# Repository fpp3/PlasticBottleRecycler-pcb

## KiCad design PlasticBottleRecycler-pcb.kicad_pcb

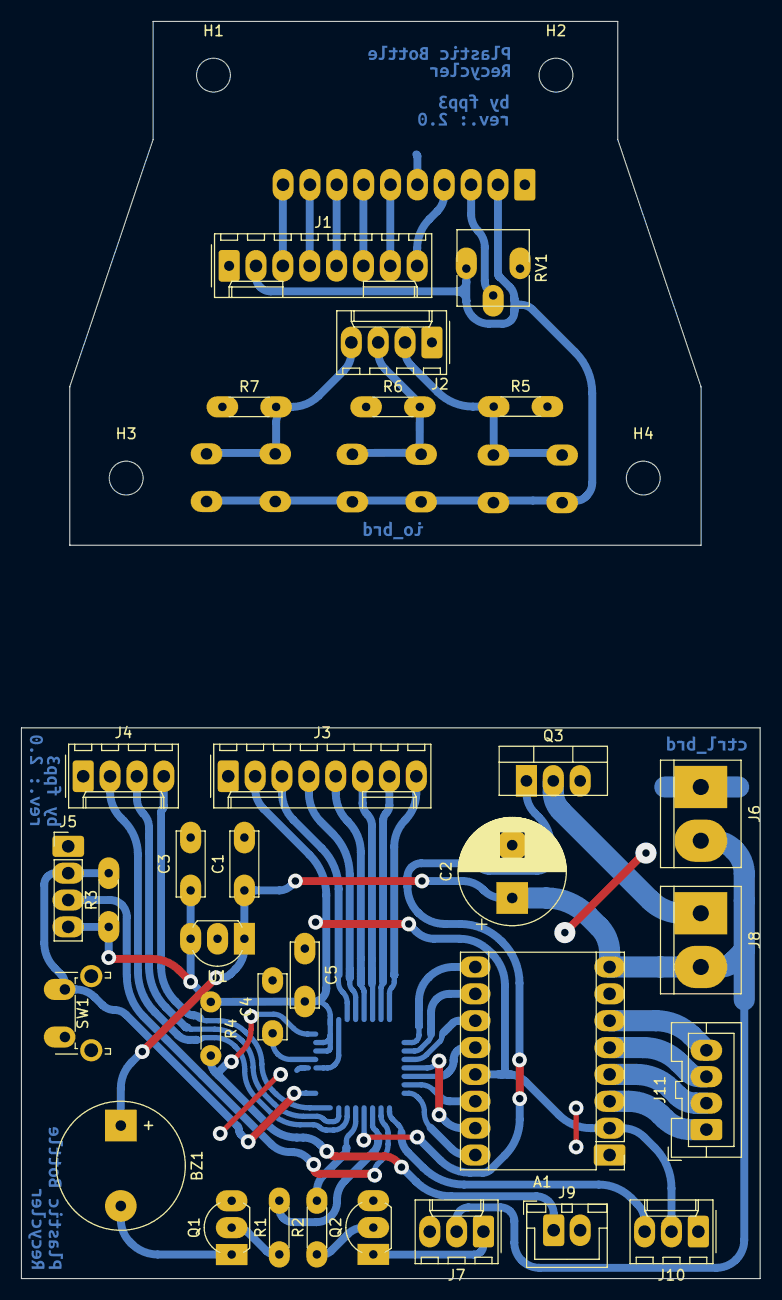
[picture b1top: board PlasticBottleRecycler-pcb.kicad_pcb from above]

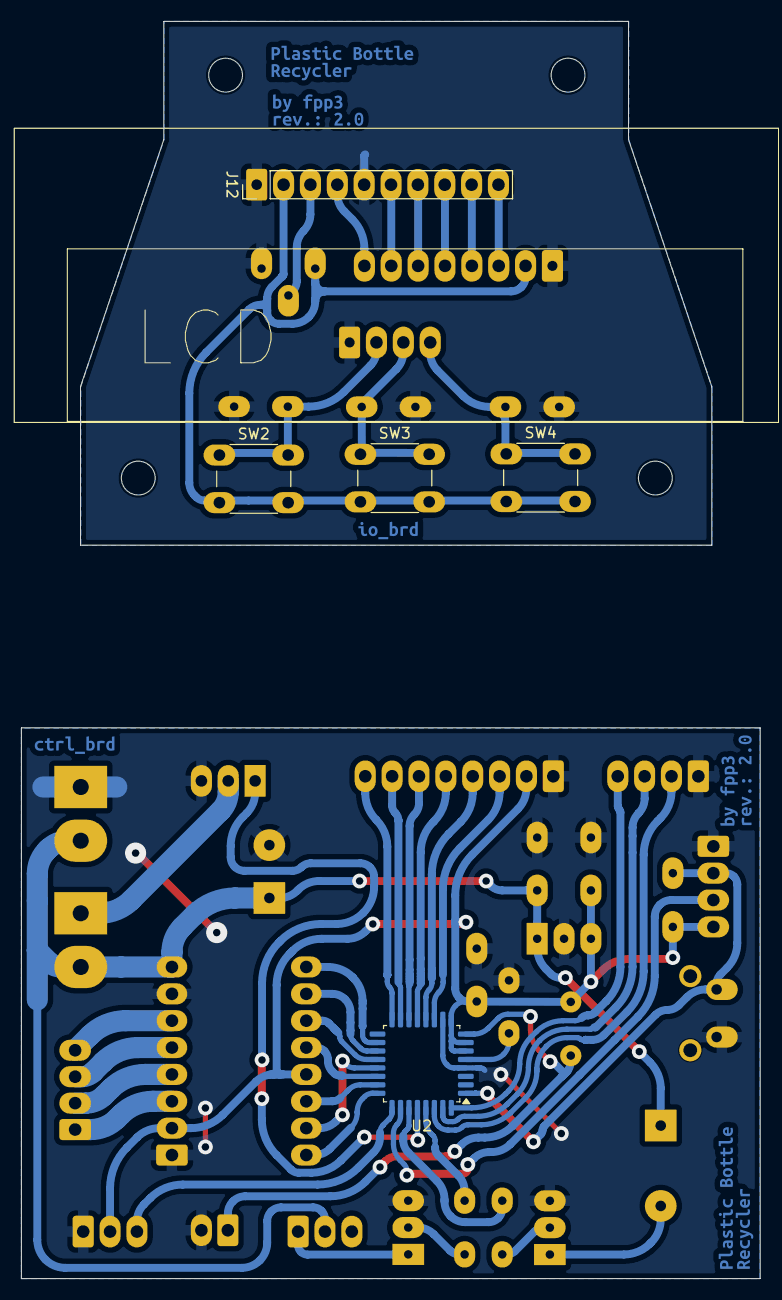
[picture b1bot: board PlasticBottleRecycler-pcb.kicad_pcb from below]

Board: 2 copper layers, 69.8 x 118.9 mm, 46 parts (11 on the bottom side), 48 nets.

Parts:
A1: Pololu_Breakout_A4988; Pololu_Breakout-16_15.2x20.3mm
BZ1: Buzzer; Buzzer_12x9.5RM7.6
C1: 330nF; C_Disc_D6.0mm_W2.5mm_P5.00mm
C2: 1000u; CP_Radial_D10.0mm_P5.00mm
C3: 100nF; C_Disc_D6.0mm_W2.5mm_P5.00mm
C4, C5: 100n; C_Disc_D6.0mm_W2.5mm_P5.00mm
H1, H2, H3, H4: MountingHole; MountingHole_3.2mm_M3
J1, J3: Conn_01x08; Molex_KK-254_AE-6410-08A_1x08_P2.54mm_Vertical
J2, J4: Conn_01x04; Molex_KK-254_AE-6410-04A_1x04_P2.54mm_Vertical
J5: SWIM; PinHeader_1x04_P2.54mm_Vertical
J6: +12V; TerminalBlock_bornier-2_P5.08mm
J7: FAN1; Molex_KK-254_AE-6410-03A_1x03_P2.54mm_Vertical
J8: HEATER; TerminalBlock_bornier-2_P5.08mm
J9: NTC; JST_XH_B2B-XH-A_1x02_P2.50mm_Vertical
J10: RUNOUT; Molex_KK-254_AE-6410-03A_1x03_P2.54mm_Vertical
J11: STEPPER; JST_XA_B04B-XASK-1_1x04_P2.50mm_Vertical
J12: LCD; PinHeader_1x10_P2.54mm_Vertical
Q1, Q2: BC337; TO-92L_Inline_Wide
Q3: IRF3205; TO-220-3_Vertical
R1, R2: 680; R_Axial_DIN0204_L3.6mm_D1.6mm_P5.08mm_Horizontal
R3, R5, R6, R7: 10K; R_Axial_DIN0204_L3.6mm_D1.6mm_P5.08mm_Horizontal
R4: 4K7; R_Axial_DIN0204_L3.6mm_D1.6mm_P5.08mm_Horizontal
RV1: 100K; Potentiometer_Vishay_T73YP_Vertical
SW1: RESET; SW_Tactile_SPST_Angled_PTS645Vx39-2LFS
SW2: BTN_PLUS; SW_PUSH_6mm_H7.3mm
SW3: BTN_OK; SW_PUSH_6mm_H7.3mm
SW4: BTN_MINUS; SW_PUSH_6mm_H7.3mm
U1: LM7805_TO220; TO-92L_Inline_Wide
U2: STM8S005K6T6C; LQFP-32_7x7mm_P0.8mm
kibuzzard-67C3B0C4: G***; kibuzzard-67C3B0C4
kibuzzard-67C3947F: G***; kibuzzard-67C3947F
kibuzzard-67C39444, kibuzzard-67C39444#2: G***; kibuzzard-67C39444
kibuzzard-67C39452, kibuzzard-67C39452#2: G***; kibuzzard-67C39452

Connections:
/Controller Board/+5V: A1.2 (VDD), A1.13 (~RESET), C3.1, C5.2, J3.2, J5.4, J10.2, R3.1, R4.1, U1.3 (VO), U2.6 (VDD), U2.7 (VDDIO), U2.9 (VDDA)
/Controller Board/+12V: A1.8 (VMOT), BZ1.1 (+), C1.1, C2.1, J6.2, J7.2, J8.2, U1.1 (VI)
/Controller Board/A4988_DIR: A1.16 (DIR), U2.24 (SPI_MISO/PC7)
/Controller Board/A4988_ENA: A1.9 (~ENABLE), U2.18 (PC1/TIM1_CH1/UART2_CLK)
/Controller Board/A4988_MS1: A1.10 (MS1), U2.19 (PC2/TIM1_CH2)
/Controller Board/A4988_MS2: A1.11 (MS2), U2.20 (PC3/TIM1_CH3)
/Controller Board/A4988_MS3: A1.12 (MS3), U2.22 (SPI_SCK/PC5)
/Controller Board/A4988_SLP: A1.14 (~SLEEP), U2.23 (SPI_MOSI/PC6)
/Controller Board/A4988_STP: A1.15 (STEP), U2.21 (PC4/TIM1_CH4)
/Controller Board/BTN_MINUS: J4.4, U2.32 (TLI/TIM1_CH4/PD7)
/Controller Board/BTN_OK: J4.3, U2.31 (UART2_RX/PD6)
/Controller Board/BTN_PLUS: J4.2, U2.30 (UART2_TX/PD5)
/Controller Board/BUZZER: R1.1, U2.27 (TIM3_CH1/TIM2_CH3/PD2)
/Controller Board/FAN1: R2.1, U2.29 (TIM2_CH1/BEEP/PD4)
/Controller Board/GND: A1.1 (GND), A1.7 (GND), C1.2, C2.2, C3.2, C4.2, C5.1, J3.1, J4.1, J5.1, J6.1, J9.2, J10.1, Q1.3 (E), Q2.3 (E), Q3.3 (S), SW1.1, U1.2 (GND), U2.4 (VSS), U2.10 (VSSA)
/Controller Board/HEATER: Q3.1 (G), U2.28 (TIM2_CH2/ADC_ETR/PD3)
/Controller Board/LCD_D4: J3.6, U2.14 (PB2/TIM1_CH3N/AIN2)
/Controller Board/LCD_D5: J3.5, U2.13 (PB3/TIM1_ETR/AIN3)
/Controller Board/LCD_D6: J3.4, U2.12 (PB4/I2C_SCL/AIN4)
/Controller Board/LCD_D7: J3.3, U2.11 (PB5/I2C_SDA/AIN5)
/Controller Board/LCD_EN: J3.7, U2.15 (PB1/TIM1_CH2N/AIN1)
/Controller Board/LCD_RS: J3.8, U2.16 (PB0/TIM1_CH1N/AIN0)
/Controller Board/RESET: J5.2, R3.2, SW1.2, U2.1 (~RST)
/Controller Board/RUNOUT: J10.3, U2.25 (TIM3_CH2/TIM1_BKIN/CLK_CCO/PD0)
/Controller Board/SWIM: J5.3, U2.26 (SWIM/PD1)
/IO Board/+5V: J1.2, J12.2, RV1.1, SW2.2, SW3.2, SW4.2
/IO Board/BTN_MINUS: J2.4, R7.2, SW4.1
/IO Board/BTN_OK: J2.3, R6.2, SW3.1
/IO Board/BTN_PLUS: J2.2, R5.1, SW2.1
/IO Board/GND: J1.1, J2.1, J12.1, J12.5, R5.2, R6.1, R7.1, RV1.3
/IO Board/LCD_D4: J1.6, J12.7
/IO Board/LCD_D5: J1.5, J12.8
/IO Board/LCD_D6: J1.4, J12.9
/IO Board/LCD_D7: J1.3, J12.10
/IO Board/LCD_EN: J1.7, J12.6
/IO Board/LCD_RS: J1.8, J12.4
unnamed: A1.4 (1A), J11.2
unnamed: A1.3 (1B), J11.1
unnamed: A1.5 (2A), J11.3
unnamed: A1.6 (2B), J11.4
unnamed: BZ1.2 (-), Q1.1 (C)
unnamed: J7.1, Q2.1 (C)
unnamed: J8.1, Q3.2 (D)
unnamed: J9.1, R4.2, U2.8 (AIN12/PF4)
unnamed: J12.3, RV1.2
unnamed: Q1.2 (B), R1.2
unnamed: Q2.2 (B), R2.2
unnamed: C4.1, U2.5 (VCAP)

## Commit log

2025-01-24 Add Schematic
2025-01-24 Add .gitignore
2025-01-25 Add PCB design
2025-02-28 Update to KiCad 9
2025-02-28 Remove unnecesary voltage regulator
2025-02-28 update to kicad 9 (whoopsie)
2025-03-02 Revision 2.0
2025-03-05 Minor Changes
2025-03-08 Restored pad copper layers to "all layers"
